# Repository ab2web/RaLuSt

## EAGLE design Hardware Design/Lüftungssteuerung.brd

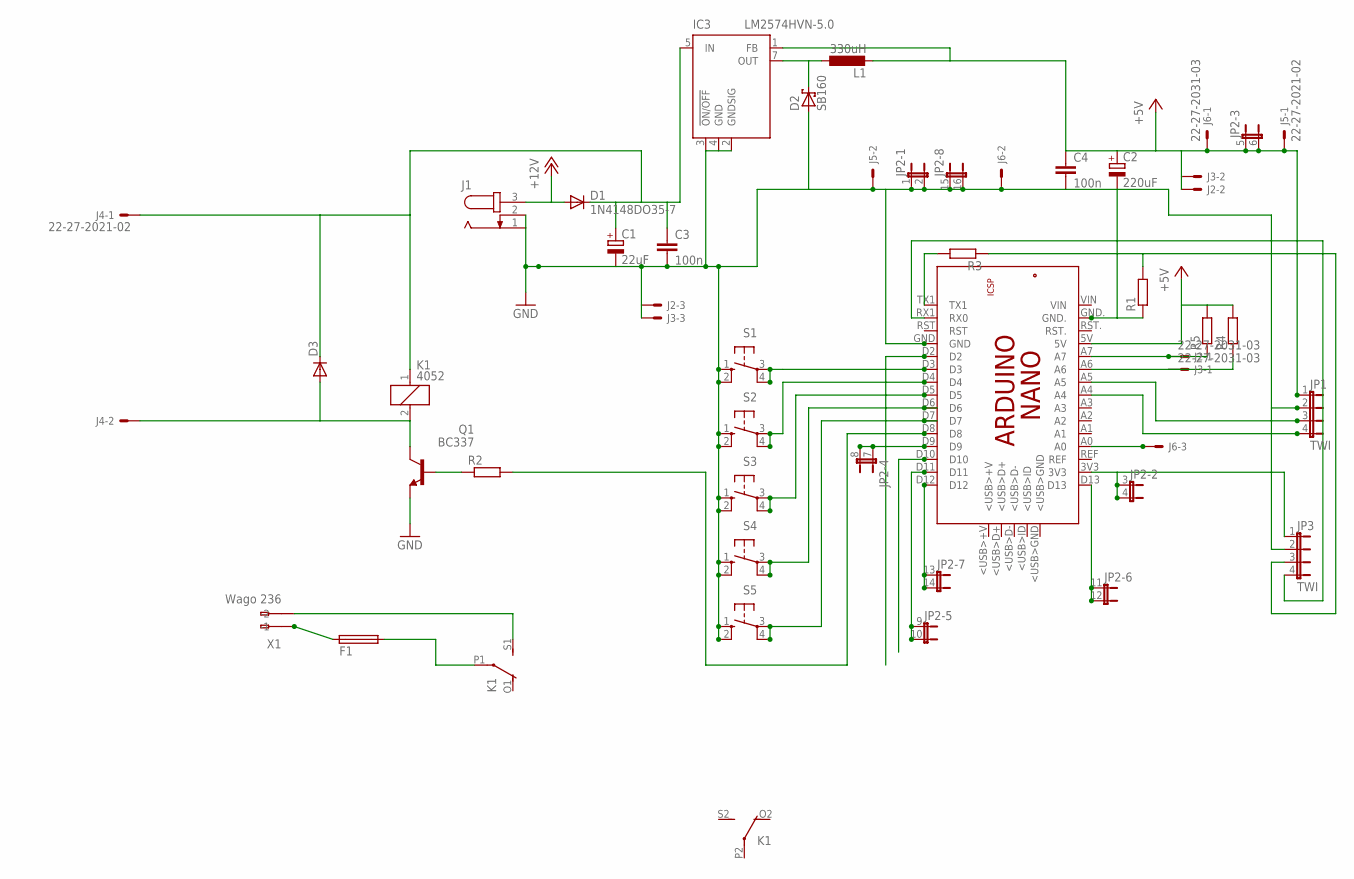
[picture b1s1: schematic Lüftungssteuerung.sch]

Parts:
C1: 22uF; E2-5
C2: 220uF; E5-10,5
C3, C4: 100n; C1206
D1: 1N4148DO35-7; DO35-7
D2: SB160; DO41-7.6
D3: DIODE-DO41-7.6; DO41-7.6
F1: SH22,5
IC3: LM2574HVN-5.0; DIL08
J1: JACK-PLUG0; SPC4077
J2, J3, J6: 22-27-2031-03; 6410-03
J4, J5: 22-27-2021-02; 6410-02
JP1, JP3: TWI; JP4
JP2: JP8QE; JP8Q
K1: 4052; F4052
L1: 330uH; PIS47XX
PCB1: ARDUINO_NANO
Q1: BC337; TO92
R1, R2, R3, R4, R5: R-EU_R1206; R1206
S1, S2, S3, S4, S5: 10-XX; B3F-10XX
X1: Wago 236; 255-402-508

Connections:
+5V: C2.+, C4.1, IC3.1 (FB), J2.2, J3.2, J5.1, J6.1, JP1.1, JP2.5 (1), JP2.6 (2), L1.1 (2), PCB1.5V, R4.2, R5.2
+12V: D1.A, J1.3
GND: C1.-, C2.-, C3.2, C4.2, D2.A, IC3.2 (GNDSIG), IC3.3 (!ON/OFF), IC3.4 (GND), J1.1, J1.2, J2.3, J3.3, J5.2, J6.2, JP1.2, JP2.1, JP2.2, JP2.15 (1), JP2.16 (2), JP3.2, PCB1.GND, PCB1.GND., Q1.1 (E), R1.1, S1.1 (S), S1.2 (S1), S2.1 (S), S2.2 (S1), S3.1 (S), S3.2 (S1), S4.1 (S), S4.2 (S1), S5.1 (S), S5.2 (S1)
unnamed: C1.+, C3.1, D1.C, D3.C, IC3.5 (IN), J4.1, K1.1
unnamed: JP1.3, PCB1.A5
unnamed: J2.1, PCB1.A7, R5.1
unnamed: J3.1, PCB1.A6, R4.1
unnamed: JP1.4, PCB1.A4
unnamed: JP2.7 (1), JP2.8 (2), PCB1.D9
unnamed: J6.3, PCB1.A0
unnamed: JP3.4, PCB1.RX1 (RX0)
unnamed: PCB1.TX1, R3.2
unnamed: JP3.3, R1.2, R3.1
unnamed: JP2.11 (1), JP2.12 (2), PCB1.D13
unnamed: PCB1.D3, S1.3, S1.4 (P1)
unnamed: PCB1.D4, S2.3, S2.4 (P1)
unnamed: D3.A, J4.2, K1.2, Q1.3 (C)
unnamed: Q1.2 (B), R2.1
unnamed: PCB1.D7, S5.3, S5.4 (P1)
unnamed: JP2.3 (1), JP2.4 (2), JP3.1, PCB1.3V3
unnamed: JP2.13 (1), JP2.14 (2), PCB1.D12
unnamed: JP2.9 (1), JP2.10 (2), PCB1.D11
unnamed: PCB1.D6, S4.3, S4.4 (P1)
unnamed: PCB1.D5, S3.3, S3.4 (P1)
unnamed: PCB1.D8, R2.2
unnamed: K1.S1 (S), X1.A2 (-2)
unnamed: F1.2, K1.P1
unnamed: F1.1, X1.A1 (-1)
unnamed: D2.C, IC3.7 (OUT), L1.2 (1)

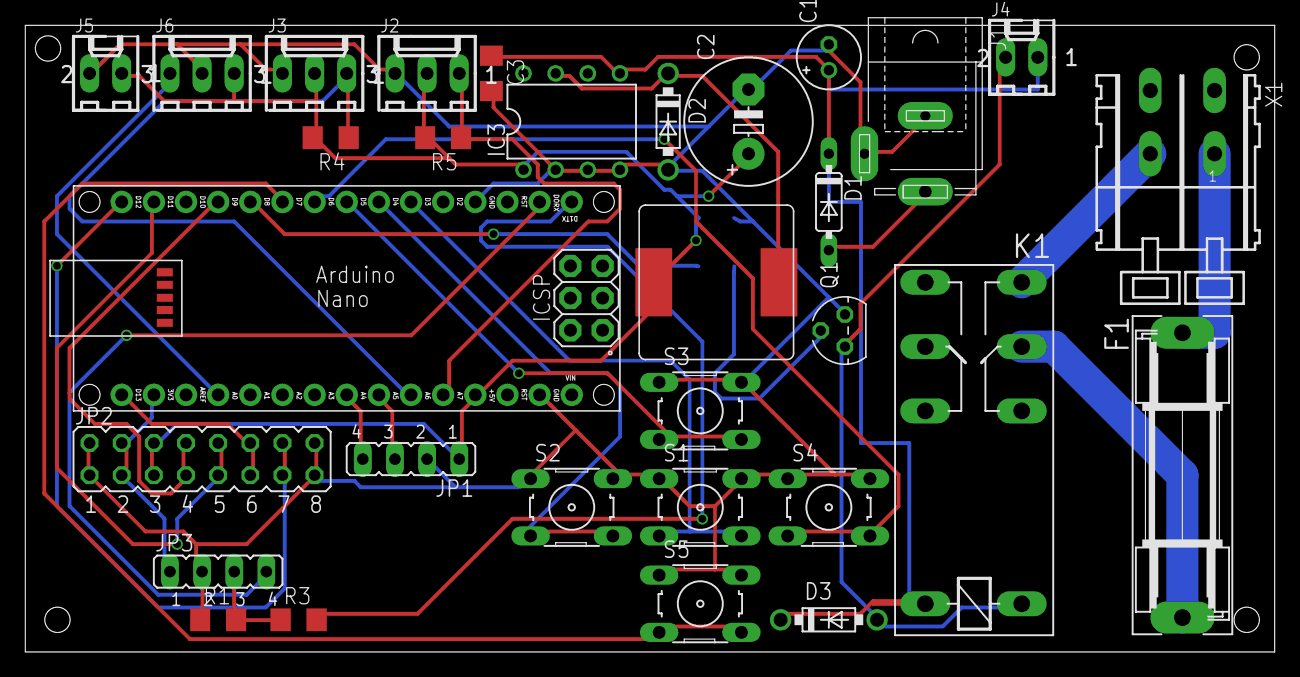
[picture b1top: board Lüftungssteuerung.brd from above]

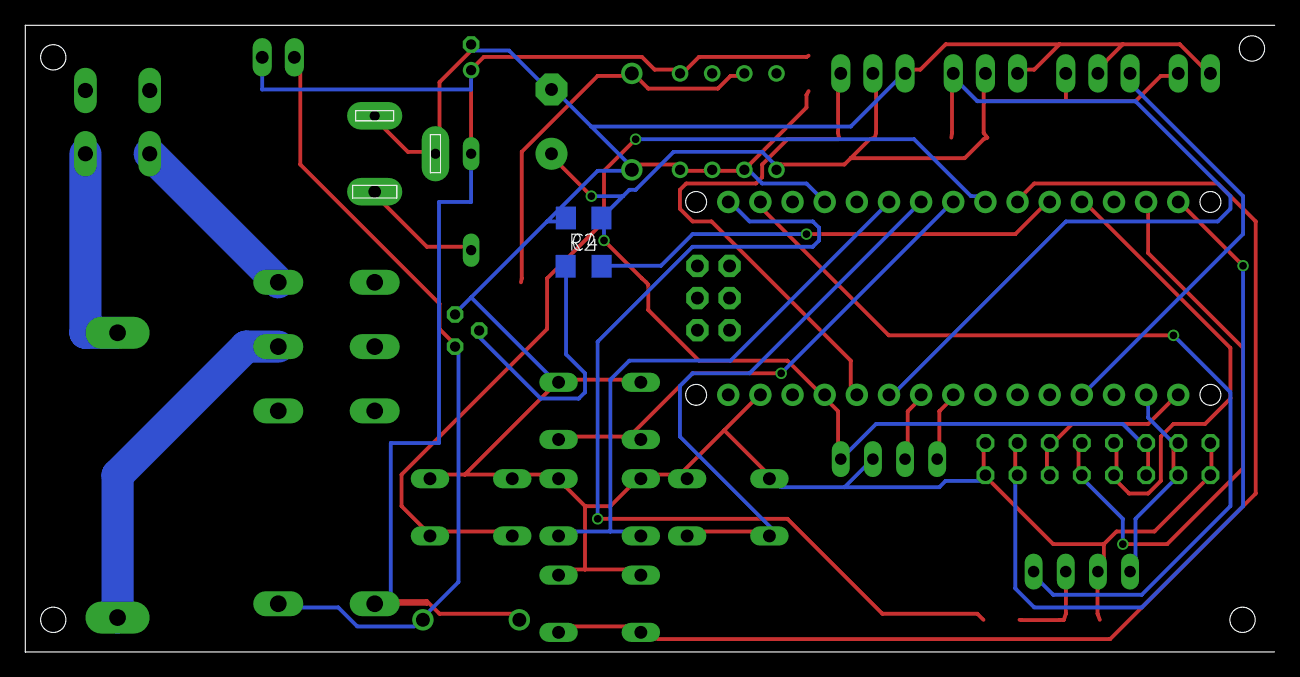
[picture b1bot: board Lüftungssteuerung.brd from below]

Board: 2 copper layers, 98.7 x 49.5 mm, 33 parts (2 on the bottom side), 29 nets.

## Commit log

2015-04-09 Create HW
2015-04-09 HW Initial Release
    Achtung Fehlerhaft
2015-04-22 initial commit
    initial commit of the softwaredesign
